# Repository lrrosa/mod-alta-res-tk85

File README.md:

# Mod Alta Resolução para o TK-85 ("Maldonado")

Reconstrução em **KiCad 10** do esquema elétrico da modificação de alta-resolução
gráfica para o **TK-85** (clone brasileiro do Sinclair ZX81), publicada por
**Milton Maldonado Jr.** na revista *Microhobby*.

O circuito acrescenta um framebuffer gráfico de alta resolução ao TK-85: três SRAMs
6116 compartilham o espaço de endereços da ROM principal (2364 — que contém o BASIC
e também as tabelas de caracteres) e são varridas por contadores sincronizados com a
geração de vídeo, dando uma definição comparável à de micros bem mais caros da época.

> **Status:** esquema verificado (ERC 0/0), PCB roteada (DRC 0/0) e Gerbers prontos
> para fabricação — falta montar e testar em hardware real.
> Veja [Estado do projeto](#estado-do-projeto).

---

## Estrutura do repositório

```
mod-alta-res-tk85/
├── kicad/                     Projeto KiCad 10
│   ├── mod_tk85_hires.kicad_sch    Esquema (folha única)
│   ├── mod_tk85_hires.kicad_pcb    Placa (roteada, 2 camadas, DRC limpo)
│   ├── mod_tk85_hires.kicad_pro    Projeto
│   ├── sym-lib-table               Tabela de símbolos (caminhos ${KIPRJMOD})
│   └── sym/                        Símbolos personalizados (ROM 2364, SRAM 6116)
├── esquemas/                  Esquema e placa exportados (PDF e SVG)
├── fabricacao/                Gerbers + furação (zip pronto para fábrica)
├── docs/                      Documentação, errata, BOM, mecânica
└── README.md
```

## Como abrir

Abra `kicad/mod_tk85_hires.kicad_pro` no KiCad 10. Os símbolos das memórias vêm da
biblioteca local em `kicad/sym/` (referenciada por caminho relativo `${KIPRJMOD}`, de
modo que o projeto pode ser movido ou clonado sem quebrar). Os demais símbolos (74xx,
Device, Connector, power) vêm das bibliotecas padrão do KiCad.

## Como funciona (resumo)

| Bloco | CI | Função |
|-------|----|--------|
| Framebuffer | U1–U3 (6116) | 3× 2 KB de SRAM gráfica, no espaço das tabelas de caracteres |
| ROM principal | U4 (2364) | ROM original do TK-85 (BASIC + caracteres), remanejada para a placa do mod |
| Contadores de vídeo | U5, U6 (74LS93) | Geram o endereço de varredura sincronizado ao vídeo |
| Multiplexador | U7 (74LS157) | Chaveia endereço: CPU (RFSH=1) × contadores (RFSH=0) |
| Decodificador | U8 (74LS138) | Seleciona qual das 3 SRAMs (`/CS0..2`) via A11/A12 |
| Cola lógica | U9 (74LS00) | Inversor de A14 para gerar `RAM CS` |
| Ajuste de reset | RV1 (22K) | Trimpot de temporização do reset dos contadores (errata) |

A conexão física com o TK-85 é feita por um **interposer pass-through**: os dois
pentes de 12 pinos (`IC2_PINS_1_12`, `IC2_PINS_13_24`) encaixam no soquete da ROM
principal (IC2) do TK-85, e a ROM 2364 encaixa por cima — cada pino do soquete é
eletricamente o mesmo nó do pino correspondente da ROM.

Descrição detalhada em [`docs/descricao-circuito.md`](docs/descricao-circuito.md).

## Errata

O artigo tem alguns erros, omissões e ambiguidades, já **corrigidos** aqui. Não os
"desfaça" comparando com a revista. Detalhes em
[`docs/correcoes-errata.md`](docs/correcoes-errata.md). Em resumo:

- `/WE` das 6116 → `WR` do Z80 (pino 22); `/OE` das 6116 → GND (omissão do artigo).
- Trimpot de 15–22 K no reset dos dois 74LS93 (`RV1`).
- Pino 9 do primeiro 74LS93 → **pino 5** do 74LS157 (o texto do artigo diz pino 9).
- `/CS` da ROM (pino 20 do IC2) ligado à ROM `U4` — necessário porque nesta
  implementação a ROM é remanejada para a placa do mod.

## Estado do projeto

- [x] Esquema elétrico em KiCad 10, com ERC limpo (0 erros / 0 avisos)
- [x] Nets com nomes significativos, desacoplamento e entradas não usadas amarradas
- [x] BOM ([`docs/bom.csv`](docs/bom.csv))
- [x] PCB: contorno (medido sobre a placa real) e posicionamento — ver
      [`docs/mecanica.md`](docs/mecanica.md)
- [x] PCB: roteamento completo em 2 camadas, DRC zerado (0 violações elétricas,
      0 pads desconectados); silk revisado
- [x] Gerbers e furação prontos para fabricação
      ([`fabricacao/`](fabricacao/))
- [ ] Montagem e teste em hardware real

## Créditos

- **Circuito original:** Milton Maldonado Jr. (*Microhobby*).
- **Reconstrução do esquema em KiCad:** Leonardo Roman da Rosa.

## Licença

Este projeto de hardware é licenciado sob a **CERN Open Hardware Licence v2 —
Strongly Reciprocal** (`CERN-OHL-S-2.0`). Veja o arquivo [`LICENSE`](LICENSE).

Conforme a seção 3.3 da licença, a localização da fonte (*Source Location*) deste
projeto é: <https://github.com/lrrosa/mod-alta-res-tk85>. Se você distribuir produtos
ou projetos derivados, mantenha as atribuições e disponibilize as fontes completas
sob a mesma licença.

> O material de referência original (o artigo da *Microhobby* e os datasheets dos
> componentes) **não** é redistribuído aqui por ser protegido por direitos autorais.
> Veja [`docs/referencias.md`](docs/referencias.md).

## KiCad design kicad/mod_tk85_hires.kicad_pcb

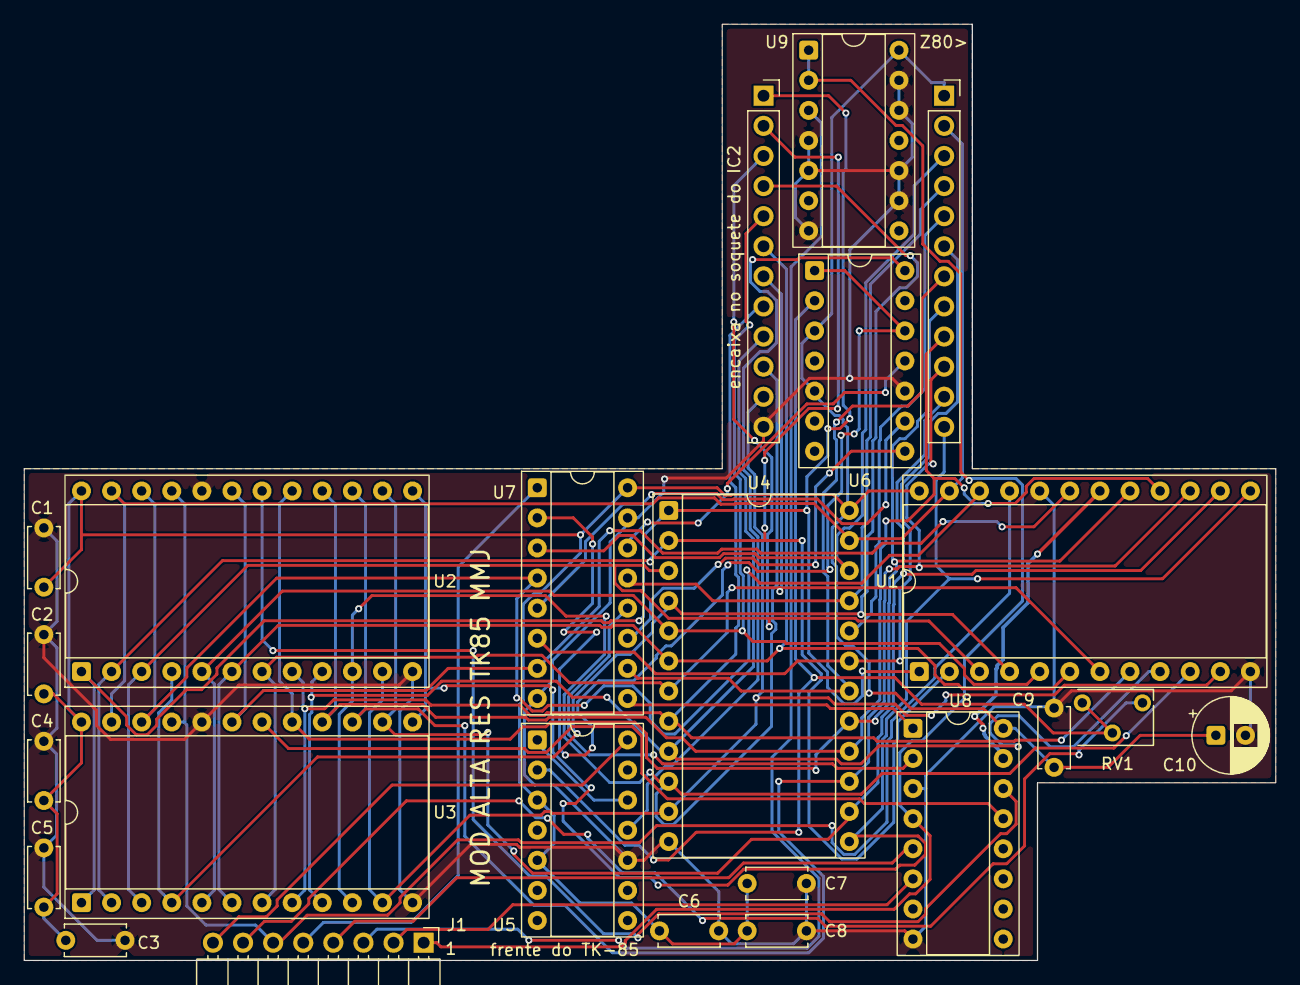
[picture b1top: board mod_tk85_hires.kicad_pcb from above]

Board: 2 copper layers, 105.6 x 79.0 mm, 23 parts (0 on the bottom side), 46 nets.

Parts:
C1, C2, C3, C4, C5, C6, C7, C8, C9: C_Disc_D5.0mm_W2.5mm_P5.00mm
C10: CP_Radial_D6.3mm_P2.50mm
IC2_PINS_1_12, IC2_PINS_13_24: PinSocket_1x12_P2.54mm_Vertical
J1: PinHeader_1x08_P2.54mm_Horizontal
RV1: 22K; Potentiometer_Bourns_3266W_Vertical
U1, U2, U3, U4: DIP-24_W15.24mm_Socket
U5, U6, U9: DIP-14_W7.62mm_Socket
U7, U8: DIP-16_W7.62mm_Socket

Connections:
+5V: C1.1, C2.1, C3.1, C4.1, C5.1, C6.1, C7.1, C8.1, C9.1, C10.1, IC2_PINS_13_24.1, U1.24, U2.24, U3.24, U4.24, U5.3, U5.5, U6.3, U6.5, U7.16, U8.16, U9.14
/A0: IC2_PINS_1_12.8, U1.8, U2.8, U3.8, U4.8
/A1: IC2_PINS_1_12.7, U1.7, U2.7, U3.7, U4.7
/A2: IC2_PINS_1_12.6, U1.6, U2.6, U3.6, U4.6
/A3: IC2_PINS_1_12.5, U1.5, U2.5, U3.5, U4.5
/A4: IC2_PINS_1_12.4, U1.4, U2.4, U3.4, U4.4
/A5: IC2_PINS_1_12.3, U1.3, U2.3, U3.3, U4.3
/A6: IC2_PINS_1_12.2, U1.2, U2.2, U3.2, U4.2
/A7: IC2_PINS_1_12.1, U1.1, U2.1, U3.1, U4.1
/A8: IC2_PINS_13_24.2, U1.23, U2.23, U3.23, U4.23
/A9: IC2_PINS_13_24.3, U4.22, U7.3
/A10: IC2_PINS_13_24.6, U4.19, U7.6
/A11: IC2_PINS_13_24.7, U4.18, U7.10
/A12: IC2_PINS_13_24.4, U4.21, U7.13
/A14: J1.1, U8.4, U9.1, U9.2
/A15: J1.2, U8.6
/CLK_60: J1.7, RV1.1
/CLK_VID: J1.8, U5.14
/CNT_RST: RV1.2, RV1.3, U5.2, U6.2
/CS0: U1.18, U8.15
/CS1: U2.18, U8.14
/CS2: U3.18, U8.13
/CS_ROM: IC2_PINS_13_24.5, U4.20
/CTA_Q0: U5.1, U5.12
/CT_CARRY: U5.11, U6.14
/D0: IC2_PINS_1_12.9, U1.9, U2.9, U3.9, U4.9
/D1: IC2_PINS_1_12.10, U1.10, U2.10, U3.10, U4.10
/D2: IC2_PINS_1_12.11, U1.11, U2.11, U3.11, U4.11
/D3: IC2_PINS_13_24.12, U1.13, U2.13, U3.13, U4.13
/D4: IC2_PINS_13_24.11, U1.14, U2.14, U3.14, U4.14
/D5: IC2_PINS_13_24.10, U1.15, U2.15, U3.15, U4.15
/D6: IC2_PINS_13_24.9, U1.16, U2.16, U3.16, U4.16
/D7: IC2_PINS_13_24.8, U1.17, U2.17, U3.17, U4.17
/MREQ: J1.4, U8.5
/RAM_A9: U1.22, U2.22, U3.22, U7.4
/RAM_A10: U1.19, U2.19, U3.19, U7.7
/RAM_CS: J1.3, U9.3
/RFSH: J1.5, U7.1
/SEL_A0: U7.9, U8.1
/SEL_A1: U7.12, U8.2
/VQ0: U6.1, U6.12, U7.2
/VQ1: U6.9, U7.5
/VQ2: U6.8, U7.11
/VQ3: U6.11, U7.14
/WR: J1.6, U1.21, U2.21, U3.21
GND: C1.2, C2.2, C3.2, C4.2, C5.2, C6.2, C7.2, C8.2, C9.2, C10.2, IC2_PINS_1_12.12, U1.12, U1.20, U2.12, U2.20, U3.12, U3.20, U4.12, U5.10, U6.10, U7.8, U7.15, U8.3, U8.8, U9.4, U9.5, U9.7, U9.9, U9.10, U9.12, U9.13

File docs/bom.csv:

"Ref","Valor","Footprint","Qtd"
"C1-C9","100nF","Capacitor_THT:C_Disc_D5.0mm_W2.5mm_P5.00mm","9"
"C10","47uF","Capacitor_THT:CP_Radial_D6.3mm_P2.50mm","1"
"IC2_PINS_1_12","IC2 pinos 1-12","Connector_PinSocket_2.54mm:PinSocket_1x12_P2.54mm_Vertical","1"
"IC2_PINS_13_24","IC2 pinos 13-24","Connector_PinSocket_2.54mm:PinSocket_1x12_P2.54mm_Vertical","1"
"J1","Sinais do TK-85","Connector_PinHeader_2.54mm:PinHeader_1x08_P2.54mm_Horizontal","1"
"RV1","22K","Potentiometer_THT:Potentiometer_Bourns_3266W_Vertical","1"
"U1-U3","6116","Package_DIP:DIP-24_W15.24mm_Socket","3"
"U4","2364 (IC2)","Package_DIP:DIP-24_W15.24mm_Socket","1"
"U5,U6","74LS93","Package_DIP:DIP-14_W7.62mm_Socket","2"
"U7","74LS157","Package_DIP:DIP-16_W7.62mm_Socket","1"
"U8","74LS138","Package_DIP:DIP-16_W7.62mm_Socket","1"
"U9","74LS00","Package_DIP:DIP-14_W7.62mm_Socket","1"
